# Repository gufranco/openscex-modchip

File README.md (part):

<div align="center">

<h1>openscex-modchip</h1>

<strong>Stealth SCEx region unlock for the PlayStation and PSone, on an ATtiny85 that <a href="src/trim.c">trims its own clock</a> against the console.</strong>

English | [日本語](README.ja.md) | [中文](README.zh.md)

<br>

<p>
  <a href="#quick-start">Quick start</a> |
  <a href="#console-tap-points">Wiring</a> |
  <a href="#status-indicator">Status indicator</a> |
  <a href="#against-other-chips">Comparison</a> |
  <a href="../../issues/new?template=compatibility.yml">Report your console</a>
</p>

</div>

[**6084**](Makefile) bytes of flash · [**8**](assets/psnee) board families, PU-7 to PM-41(2) · [**3**](src/region.c) regions · [**0**](AGENTS.md) MISRA deviations · [**100%**](tests/host) host line and branch coverage · [**669/669**](tools/mutate.py) mutants killed

```bash
gh release download --repo gufranco/openscex-modchip --pattern 'openscex-modchip-attiny85.hex' --pattern SHA256SUMS
sha256sum -c SHA256SUMS --ignore-missing
avrdude -c <programmer> -p attiny85 -U flash:w:openscex-modchip-attiny85.hex:i
```

> [!IMPORTANT]
> The current firmware passes the full simulation gate and has not yet run on a console. Measure the tap voltages before wiring. Source: [compatibility reports](https://github.com/gufranco/openscex-modchip/issues?q=label%3Acompatibility), [tests/sim](tests/sim).

Region-unlock firmware for the original PlayStation and the PSone, on an ATtiny85. It sends the configured region string only inside the SUBQ region-check window and keeps DATA high-impedance the rest of the time. It does not patch the boot ROM, so Japanese fat consoles and the PAL PSone also need a patched BIOS. It is not an optical-drive emulator, does not support PS2 or Saturn, and does not defeat LibCrypt. Source: [src/run.c](src/run.c), [src/inject.c](src/inject.c), [AGENTS.md](AGENTS.md).

| | | Source |
|:--|:--|:--|
| **Silent after acceptance**<br>No string starts after the first program-area frame; one already under way finishes, within 181 ms. Only a new lead-in read, such as an anti-mod TOC re-read, is served again. | **Disc swaps without a lid wire**<br>1.5 s without SUBQ frames counts as a swap and re-arms the chip for the next disc. | [src/inject.c](src/inject.c), [src/loop.c](src/loop.c), [src/run.c](src/run.c) |
| **Self-trimmed timing**<br>The chip times the console's 75 Hz SUBQ frames and trims its internal oscillator to within 1%. No clock wire. | **One region, one window**<br>Only the configured region string, only inside the SUBQ region-check window, at most 16 strings per arming. | [src/trim.c](src/trim.c), [src/region.c](src/region.c), [include/pscu/config.h](include/pscu/config.h) |
| **Status LED**<br>One pin reports boot stages, each disc's result and wiring faults. A final build only blinks briefly and reports each fault once. | **Proven in code**<br>MISRA C:2012 clean, 100% host coverage, a simavr console model, mutation testing, byte-identical rebuilds. | [src/indicator.c](src/indicator.c), [tests/host](tests/host), [tools/mutate.py](tools/mutate.py) |

## Overview

| Property | Value | Source |
|:---------|:------|:--|
| Console targets | PlayStation fat PU-7 through PU-23, PSone PM-41 and PM-41(2) | [assets/psnee](assets/psnee), [PsNee PSNee.ino L372-L406](https://github.com/kalymos/PsNee/blob/df52aec97d4e1677e3ed3ead1fba0bf102b1cfd7/PSNee/PSNee.ino#L372-L406) |
| MCU | ATtiny85 (8-pin DIP) | [include/port/registers.h](include/port/registers.h), [ATtiny25/45/85 datasheet 2586Q](https://ww1.microchip.com/downloads/en/DeviceDoc/Atmel-2586-AVR-8-bit-Microcontroller-ATtiny25-ATtiny45-ATtiny85_Datasheet.pdf) |
| Method | SCEx injection | [src/inject.c](src/inject.c), [psx-spx cdromdrive.md, SCEx](https://github.com/psx-spx/psx-spx.github.io/blob/6d7d1bc106a7e0b616b0330fe58401ab1ba57f0f/docs/cdromdrive.md#L1211-L1230) |
| Region | one per build, `REGION=jp\|us\|eu` (default us) | [Makefile](Makefile), [src/region.c](src/region.c) |
| Clock | the internal 8 MHz RC oscillator, trimmed against the console's SUBQ frame rate | [src/trim.c](src/trim.c), [ATtiny25/45/85 datasheet 2586Q](https://ww1.microchip.com/downloads/en/DeviceDoc/Atmel-2586-AVR-8-bit-Microcontroller-ATtiny25-ATtiny45-ATtiny85_Datasheet.pdf) |
| Wires | 4 signals (SQCK, SUBQ, DATA, WFCK) plus power; optional LED | [include/port/registers.h](include/port/registers.h), [PsNee MCU.h L453-L530](https://github.com/kalymos/PsNee/blob/df52aec97d4e1677e3ed3ead1fba0bf102b1cfd7/PSNee/MCU.h#L453-L530) |
| Toolchain | C17, MISRA C:2012 zero deviations, pinned Docker image | [Dockerfile](Dockerfile), [AGENTS.md](AGENTS.md) |

## Supported build per console

| Console | Board | `REGION` | Second region check | Source |
|:--------|:------|:---------|:--------------------|:--|
| Fat US/Canada, SCPH-1001 | PU-8 | `us` | none | [consolemods PS1 region information](https://consolemods.org/wiki/PS1:Region_Information), [PsNee PSNee.ino L10-L17](https://github.com/kalymos/PsNee/blob/df52aec97d4e1677e3ed3ead1fba0bf102b1cfd7/PSNee/PSNee.ino#L10-L17) |
| Fat US/Canada, SCPH-550x1/700x1/900x1 | PU-18 to PU-23 | `us` | none | [consolemods PS1 region information](https://consolemods.org/wiki/PS1:Region_Information), [PsNee PSNee.ino L10-L17](https://github.com/kalymos/PsNee/blob/df52aec97d4e1677e3ed3ead1fba0bf102b1cfd7/PSNee/PSNee.ino#L10-L17) |
| Fat PAL, SCPH-1002 | PU-8 | `eu` | none | [consolemods PS1 region information](https://consolemods.org/wiki/PS1:Region_Information), [PsNee PSNee.ino L10-L17](https://github.com/kalymos/PsNee/blob/df52aec97d4e1677e3ed3ead1fba0bf102b1cfd7/PSNee/PSNee.ino#L10-L17) |
| Fat PAL, SCPH-550x2/900x2 | PU-18 to PU-22 | `eu` | none | [consolemods PS1 region information](https://consolemods.org/wiki/PS1:Region_Information), [PsNee PSNee.ino L10-L17](https://github.com/kalymos/PsNee/blob/df52aec97d4e1677e3ed3ead1fba0bf102b1cfd7/PSNee/PSNee.ino#L10-L17) |
| PSone US/Canada, SCPH-101 | PM-41 / PM-41(2) | `us` | none | [consolemods PS1 region information](https://consolemods.org/wiki/PS1:Region_Information), [PsNee PSNee.ino L10-L17](https://github.com/kalymos/PsNee/blob/df52aec97d4e1677e3ed3ead1fba0bf102b1cfd7/PSNee/PSNee.ino#L10-L17) |
| PSone PAL, SCPH-102 | PM-41 / PM-41(2) | `eu` | in the boot ROM; needs a patched BIOS | [consolemods PS1 region information](https://consolemods.org/wiki/PS1:Region_Information), [PsNee PSNee.ino L33-L38](https://github.com/kalymos/PsNee/blob/df52aec97d4e1677e3ed3ead1fba0bf102b1cfd7/PSNee/PSNee.ino#L33-L38) |
| PSone Japan, SCPH-100 | PM-41 | `jp` | in the boot ROM; needs a patched BIOS | [consolemods PS1 region information](https://consolemods.org/wiki/PS1:Region_Information), [PsNee PSNee.ino L33-L38](https://github.com/kalymos/PsNee/blob/df52aec97d4e1677e3ed3ead1fba0bf102b1cfd7/PSNee/PSNee.ino#L33-L38) |
| Fat Japan, SCPH-1000/3000/3500/5000/5500/7000/7500/9000 | PU-7 to PU-23 | `jp` | in the boot ROM; needs a patched BIOS, though early SCPH-1000 units boot the disc anyway | [consolemods PS1 region information](https://consolemods.org/wiki/PS1:Region_Information), [PsNee PSNee.ino L33-L38](https://github.com/kalymos/PsNee/blob/df52aec97d4e1677e3ed3ead1fba0bf102b1cfd7/PSNee/PSNee.ino#L33-L38) |
| Asia, SCPH-xxx3 | unknown | `jp` | none | [consolemods PS1 region information](https://consolemods.org/wiki/PS1:Region_Information), [PsNee PSNee.ino L10-L17](https://github.com/kalymos/PsNee/blob/df52aec97d4e1677e3ed3ead1fba0bf102b1cfd7/PSNee/PSNee.ino#L10-L17) |
| Asia Video CD, SCPH-5903 | unknown | `jp` + `VCD_FILTER=on` | none | [consolemods PS1 region information](https://consolemods.org/wiki/PS1:Region_Information), [PsNee PSNee.ino L456-L490](https://github.com/kalymos/PsNee/blob/df52aec97d4e1677e3ed3ead1fba0bf102b1cfd7/PSNee/PSNee.ino#L456-L490) |

The PU-7 and PU-8 use the static-gate method, as in PsNee V9.0. Dev boards (DTL-H120x, PU-9) read burned discs natively and need no chip. Source: [PsNee PSNee.ino L33-L38](https://github.com/kalymos/PsNee/blob/df52aec97d4e1677e3ed3ead1fba0bf102b1cfd7/PSNee/PSNee.ino#L33-L38), [PsNee PSNee.ino L10-L17](https://github.com/kalymos/PsNee/blob/df52aec97d4e1677e3ed3ead1fba0bf102b1cfd7/PSNee/PSNee.ino#L10-L17), [PsNee PSNee.ino L456-L490](https://github.com/kalymos/PsNee/blob/df52aec97d4e1677e3ed3ead1fba0bf102b1cfd7/PSNee/PSNee.ino#L456-L490), [src/subq.c](src/subq.c).

## Quick start

Each [release](../../releases) carries prebuilt images: `us`, `eu`, `jp`, `jp-vcd` for the SCPH-5903, a quiet `-final` variant of each (see [Status indicator](#status-indicator)), a `SHA256SUMS` file, the license, `toolchain.spdx.json`, an SPDX bill of materials of the toolchain that built them, and a build-provenance attestation for every one of those files, the bill of materials included. Check a download before flashing it:

```bash
sha256sum -c SHA256SUMS --ignore-missing
gh attestation verify openscex-modchip-attiny85.hex --repo gufranco/openscex-modchip
```

Releases are versioned automatically from the commit history. To build from source, run every build, check and test through `make` in the pinned Docker toolchain; only `avrdude` runs on the host. Source: [.releaserc.json](.releaserc.json), [.github/workflows/release.yml](.github/workflows/release.yml).

| Tool | Purpose | Source |
|:-----|:--------|:--|
| Docker | runs the pinned toolchain | [Docker](https://docs.docker.com/get-docker/), [Dockerfile](Dockerfile) |
| Git | clones the repository | [Git](https://git-scm.com/downloads) |
| avrdude | flashes the image to the chip | [avrdude](https://github.com/avrdudes/avrdude) |
| Python 3.13 or later | runs make's Docker wrapper on the host | [Python](https://www.python.org/downloads/), [tools/docker_make.py](tools/docker_make.py), [pyproject.toml](pyproject.toml) |

```bash
git clone https://github.com/gufranco/openscex-modchip.git
cd openscex-modchip
make REGION=us                                        # America
make REGION=jp VCD_FILTER=on                          # SCPH-5903
make REGION=us PROFILE=final                          # America, quiet indicator
make REGION=us PROFILE=trace                          # America, debug trace on pin 2
avrdude -c <programmer> -p attiny85 -U flash:w:build/attiny85/release/openscex-modchip-attiny85.hex:i
avrdude -c <programmer> -p attiny85 -U lfuse:w:0xE2:m -U hfuse:w:0xDD:m -U efuse:w:0xFF:m
```

Any ISP works, including an Arduino as ISP. Write the flash first and the fuses last. The low fuse `0xE2` selects the internal 8 MHz oscillator, the slow-rising-power start-up delay and no clock divider (CKSEL 0010, SUT 10; datasheet Tables 6-6 and 6-7). The firmware also clears the clock prescaler at boot, so CKDIV8 cannot slow it. Reflashing erases the calibration record and oscillator trim; the chip learns them again. Source: [Arduino as ISP](https://docs.arduino.cc/built-in-examples/arduino-isp/ArduinoISP/), [ATtiny25/45/85 datasheet 2586Q](https://ww1.microchip.com/downloads/en/DeviceDoc/Atmel-2586-AVR-8-bit-Microcontroller-ATtiny25-ATtiny45-ATtiny85_Datasheet.pdf), [src/run.c](src/run.c).

A new ATtiny85 ships with CKDIV8 programmed and runs at 1 MHz, so the ISP clock must stay below 250 kHz until the fuses are written; the datasheet requires each half of the ISP clock to last more than two CPU cycles. An Arduino as ISP already does. With another programmer, add avrdude's `-B`, for example `-B 8`, for the first write. Source: [ATtiny25/45/85 datasheet 2586Q](https://ww1.microchip.com/downloads/en/DeviceDoc/Atmel-2586-AVR-8-bit-Microcontroller-ATtiny25-ATtiny45-ATtiny85_Datasheet.pdf), [avrdude manual, -B](https://avrdudes.github.io/avrdude/8.0/avrdude_3.html).

| Build | Fuses (low / high / extended) | Source |
|:------|:------------------------------|:--|
| Internal 8 MHz with brown-out detection at 2.7 V, recommended | `0xE2` / `0xDD` / `0xFF` | [ATtiny25/45/85 datasheet 2586Q](https://ww1.microchip.com/downloads/en/DeviceDoc/Atmel-2586-AVR-8-bit-Microcontroller-ATtiny25-ATtiny45-ATtiny85_Datasheet.pdf) |
| Internal 8 MHz without brown-out detection | `0xE2` / `0xDF` / `0xFF` | [ATtiny25/45/85 datasheet 2586Q](https://ww1.microchip.com/downloads/en/DeviceDoc/Atmel-2586-AVR-8-bit-Microcontroller-ATtiny25-ATtiny45-ATtiny85_Datasheet.pdf) |

Brown-out detection holds the chip in reset below 2.7 V, the ATtiny85's minimum supply for its speed grade; keep it on. The firmware also measures its supply before every string and holds back below about 2.75 V, shown as code 7. That limit still passes a 3.3 V supply 5 percent low on a chip whose bandgap reads high. Source: [ATtiny25/45/85 datasheet 2586Q](https://ww1.microchip.com/downloads/en/DeviceDoc/Atmel-2586-AVR-8-bit-Microcontroller-ATtiny25-ATtiny45-ATtiny85_Datasheet.pdf), [src/supply.c](src/supply.c).

Verify with the [Makefile](Makefile) targets:

```bash
make size        # image size; fails when less than 256 bytes of flash stay free
make test        # host tests, simavr console model and its stack check
make analyse     # formatting, lint, types, licences, MISRA and the Python tests
make repro       # every release image, built twice from clean, byte-identical
make mutate      # mutation testing on the logic layer
make mutate_platform  # mutation of run.c and engine.c, killed by the simulator
make bench_ci    # console bench: this firmware against PsNee in the same simulated console
```

CI runs the same gates on every push to `main` and every pull request, as defined in [`.github/workflows/ci.yml`](.github/workflows/ci.yml). `make mutate_platform` runs in its own workflow, [`.github/workflows/mutation.yml`](.github/workflows/mutation.yml), whenever the firmware, the simulator suite, the mutation tool or the pinned toolchain changes. `make hooks` enables the commit-message and formatting checks locally.

## MCU pinout

The four SCEx signals and the indicator pin keep PsNee's ATtiny85 assignment from its `MCU.h`, so PsNee wiring guides match pin for pin. PB5 stays RESET, so the chip remains ISP-programmable. Pin numbers are for the 8-pin PDIP; check the datasheet for SOIC. Source: [PsNee MCU.h L453-L530](https://github.com/kalymos/PsNee/blob/df52aec97d4e1677e3ed3ead1fba0bf102b1cfd7/PSNee/MCU.h#L453-L530), [include/port/registers.h](include/port/registers.h), [ATtiny25/45/85 datasheet 2586Q](https://ww1.microchip.com/downloads/en/DeviceDoc/Atmel-2586-AVR-8-bit-Microcontroller-ATtiny25-ATtiny45-ATtiny85_Datasheet.pdf).

| DIP pin | Port | Signal | Direction | Connect to | Source |
|:-------:|:-----|:-------|:----------|:-----------|:--|
| 1 | PB5 | RESET | - | leave as reset | [include/port/registers.h](include/port/registers.h), [ATtiny25/45/85 datasheet 2586Q](https://ww1.microchip.com/downloads/en/DeviceDoc/Atmel-2586-AVR-8-bit-Microcontroller-ATtiny25-ATtiny45-ATtiny85_Datasheet.pdf) |
| 2 | PB3 | INDICATOR | out, optional | status LED through a 1 kΩ resistor, or leave off | [include/port/registers.h](include/port/registers.h), [PsNee PSNee.ino L64](https://github.com/kalymos/PsNee/blob/df52aec97d4e1677e3ed3ead1fba0bf102b1cfd7/PSNee/PSNee.ino#L64) |
| 3 | PB4 | WFCK | in and out | static gate, or PU-22+ live carrier | [include/port/registers.h](include/port/registers.h), [PsNee MCU.h L453-L530](https://github.com/kalymos/PsNee/blob/df52aec97d4e1677e3ed3ead1fba0bf102b1cfd7/PSNee/MCU.h#L453-L530) |
| 4 | GND | GND | - | console ground | [ATtiny25/45/85 datasheet 2586Q](https://ww1.microchip.com/downloads/en/DeviceDoc/Atmel-2586-AVR-8-bit-Microcontroller-ATtiny25-ATtiny45-ATtiny85_Datasheet.pdf) |
| 5 | PB0 | SQCK | in | SUBQ serial clock | [include/port/registers.h](include/port/registers.h), [PsNee MCU.h L453-L530](https://github.com/kalymos/PsNee/blob/df52aec97d4e1677e3ed3ead1fba0bf102b1cfd7/PSNee/MCU.h#L453-L530) |
| 6 | PB1 | SUBQ | in | SUBQ serial data | [include/port/registers.h](include/port/registers.h), [PsNee MCU.h L453-L530](https://github.com/kalymos/PsNee/blob/df52aec97d4e1677e3ed3ead1fba0bf102b1cfd7/PSNee/MCU.h#L453-L530) |
| 7 | PB2 | DATA | out, drive-low or high-Z | SCEx injection into the mechacon | [include/port/registers.h](include/port/registers.h), [src/port.S](src/port.S) |
| 8 | VCC | VCC | - | console supply, measure first | [ATtiny25/45/85 datasheet 2586Q](https://ww1.microchip.com/downloads/en/DeviceDoc/Atmel-2586-AVR-8-bit-Microcontroller-ATtiny25-ATtiny45-ATtiny85_Datasheet.pdf) |

## Console tap points

The photos below label SQCK, SUBQ, DATA, WFCK, VCC and GND on each board; solder each wire where they are marked. The PU-18 photo shows the underside. Leave AX, DX and RESET unconnected: they belong to PsNee's boot-ROM patch. Source: [assets/psnee](assets/psnee).

<table>
<tr><td align="center" width="33%"><br><sub><b>PU-7</b>. Photo from PsNee</sub></td><td align="center" width="33%"><br><sub><b>PU-8</b>, 1-658-467-22. Photo from PsNee</sub></td><td align="center" width="33%"><br><sub><b>PU-8</b>, 1-658-467-12. Photo from PsNee</sub></td></tr>
<tr><td align="center" width="33%"><br><sub><b>PU-18</b>. Photo from PsNee</sub></td><td align="center" width="33%"><br><sub><b>PU-20</b>. Photo from PsNee</sub></td><td align="center" width="33%"><br><sub><b>PU-22</b>. Photo from PsNee</sub></td></tr>
<tr><td align="center" width="33%"><br><sub><b>PU-23</b>. Photo from PsNee</sub></td><td align="center" width="33%"><br><sub><b>PM-41</b>. Photo from PsNee</sub></td><td align="center" width="33%"><br><sub><b>PM-41(2)</b>. Photo from PsNee</sub></td></tr>
</table>

These nine photos come from [PsNee](https://github.com/kalymos/PsNee) V9.0 by kalymos and its contributors, released into the public domain under the [Unlicense](LICENSES/Unlicense.txt), and are copied here resized.

| Board family | SCPH era | DATA injection point | WFCK role | Source |
|:-------------|:---------|:---------------------|:----------|:--|
| PU-7, PU-8, PU-18, PU-20 | 1000-750x | digital NRZ output of the wobble ASIC into the mechacon | static gate | [assets/psnee](assets/psnee), [PsNee PSNee.ino L372-L406](https://github.com/kalymos/PsNee/blob/df52aec97d4e1677e3ed3ead1fba0bf102b1cfd7/PSNee/PSNee.ino#L372-L406) |
| PU-22, PU-23 | 7500-900x | CD-processor tracking line, WFCK as a fake carrier, three-wire-plus-link | live clock, sync required | [assets/psnee](assets/psnee), [PsNee PSNee.ino L372-L406](https://github.com/kalymos/PsNee/blob/df52aec97d4e1677e3ed3ead1fba0bf102b1cfd7/PSNee/PSNee.ino#L372-L406) |
| PM-41, PM-41(2) | PSone 100-103 | same tracking-line carrier method; float the chip I/O when idle on PM-41(2) | live clock | [assets/psnee](assets/psnee), [quade.co PsNee guide](https://quade.co/ps1-modchip-guide/psnee/) |

With no clock or lid wire, the chip can sit anywhere the four signal wires reach. Keep those wires short: long wires pick up noise, a known cause of Mayumi V4 failures (quade.co). Remove the clock and lid wires of an install made for an earlier release before flashing this firmware, because pin 2 is now PB3, the indicator output, and would drive against a console clock left there. Source: [src/trim.c](src/trim.c), [src/loop.c](src/loop.c), [quade.co Mayumi V4 guide](https://quade.co/ps1-modchip-guide/mayumi-v4/), [include/port/registers.h](include/port/registers.h).

## Board

One optional board holds the chip in a DIP-8 socket, so it comes out for reflashing. The console wires land on six 4 by 4 mm top-side pads with no holes, 6 mm apart along the bottom edge: WFCK, SQCK, SUBQ, DATA, VCC and GND. Every part is through-hole. The socket, a 100 nF decoupling capacitor, a 220 µF bulk capacitor and a 10 kΩ RESET pull-up are always fitted, the pull-up because the chip's internal one is weak against console noise. Three headers are optional and marked "opt" on the board, so a build fits only what it uses. The board is a KiCad 10 project with its schematic, layout and design rules, 35.6 × 34.3 mm. Source: [hardware/openscex.kicad_sch](hardware/openscex.kicad_sch), [hardware/openscex.kicad_pcb](hardware/openscex.kicad_pcb).

| Part | Fit | Purpose | Source |
|:--|:--|:--|:--|
| U1, DIP-8 socket | always | holds the ATtiny85 | [hardware/openscex.kicad_sch](hardware/openscex.kicad_sch) |
| C1, 100 nF ceramic | always | answers the chip's fast current edges at its supply pins | [hardware/openscex.kicad_sch](hardware/openscex.kicad_sch) |
| C2, 220 µF electrolytic | always | holds the supply up through pulsed loads on J2, such as an active buzzer, whose pulses would otherwise dip it through the thin supply wire; 11.2 mm tall, it may be laid flat on its leads | [hardware/openscex.kicad_sch](hardware/openscex.kicad_sch), [Panasonic FC series](https://industrial.panasonic.com/cdbs/www-data/pdf/RDF0000/ABA0000C1209.pdf) |
| R1, 10 kΩ | always | holds RESET high | [hardware/openscex.kicad_sch](hardware/openscex.kicad_sch) |
| J1, keyed 2×3 ISP header | optional | reflashing the chip | [hardware/openscex.kicad_sch](hardware/openscex.kicad_sch) |
| J2, keyed JST XH 3-pin header | optional | pin 1 GND, pin 2 VCC, pin 3 PB3 (SIG on the board), for a cable to the indicator of your choice: an LED with its resistor, an active buzzer, or a board of your own | [hardware/openscex.kicad_sch](hardware/openscex.kicad_sch), [JST XH datasheet](https://www.jst-mfg.com/product/pdf/eng/eXH.pdf) |
| J3, 6-pin header | optional | the trace image's serial line, for an FTDI TTL-232R cable | [hardware/openscex.kicad_sch](hardware/openscex.kicad_sch) |

<table>
<tr><td align="center" width="33%"><br><sub><b>The board</b>, 3D view</sub></td><td align="center" width="33%"><br><sub><b>The board</b>, top</sub></td><td align="center" width="33%"><br><sub><b>The board</b>, bottom, the ground plane</sub></td></tr>
</table>

The board is symmetric about its vertical centre line: the chip, the serial header and the row of wire pads sit on it, and the ISP header on the left is balanced by the indicator header, R1 and C1 on the right. It has two layers laid out against noise. Every track is as wide as its route allows, 1.0 mm on this board; tracks run on top where they can, so the bottom stays a ground plane under the console lines; both layers are ground-poured and stitched with 0.6 mm vias; every bend is a tangent arc of at most 45 degrees; different nets keep 1 mm apart and 0.8 mm from pads. Source: [hardware/openscex.kicad_pcb](hardware/openscex.kicad_pcb), [hardware/openscex.kicad_dru](hardware/openscex.kicad_dru).

The ISP header follows the AVR 6-pin layout: 1 MISO on SUBQ, 2 VCC, 3 SCK on DATA, 4 MOSI on SQCK, 5 RESET, 6 GND. Its keyed shroud keeps 1.5 mm clear of every other part. Reflash with the board out of the console or its wires unsoldered; in place, the programmer would feed the console's supply and fight the console's drivers on SQCK and SUBQ. Source: [hardware/openscex.kicad_sch](hardware/openscex.kicad_sch), [ATtiny25/45/85 datasheet 2586Q](https://ww1.microchip.com/downloads/en/DeviceDoc/Atmel-2586-AVR-8-bit-Microcontroller-ATtiny25-ATtiny45-ATtiny85_Datasheet.pdf).

J2 is a keyed JST XH header, so its plug goes in one way only. Its pins follow the RC servo order, GND, VCC, signal: VCC in the middle never meets a ground wire, so even a plug forced in reversed powers nothing backwards. VCC powers whatever the cable leads to, such as a buzzer module or a board of your own; a plain LED needs only GND and SIG. VCC is the console's 3.5 V rail, so a cable must never join it to GND. Source: [hardware/openscex.kicad_sch](hardware/openscex.kicad_sch), [JST XH datasheet](https://www.jst-mfg.com/product/pdf/eng/eXH.pdf).

The serial header J3 takes the 6-way socket of an FTDI TTL-232R cable: pin 1 is GND, pin 5 the cable's RXD input, and pins 2, 3, 4 and 6 stay open, so the cable's 5 V output never reaches the console. It stands at the top edge with 2 mm clear around it, so the socket meets no other part. J2 and J3 both carry PB3, and the image flashed decides what PB3 is, so plug only the cable that matches it: the indicator cable for `debug` or `final`, the serial cable for `trace`. Source: [hardware/openscex.kicad_sch](hardware/openscex.kicad_sch), [hardware/openscex.kicad_pcb](hardware/openscex.kicad_pcb), [TTL-232R datasheet](https://www.farnell.com/datasheets/81225.pdf).

The board has a bill of materials, whose Fit column names the optional parts, and a Gerber and drill archive ready for a board house, both exported with KiCad 10.0.6. Teardrops are drawn into the board, so the archive needs no refill in KiCad. Source: [hardware/openscex-bom.csv](hardware/openscex-bom.csv), [hardware/fab/openscex-gerbers.zip](hardware/fab/openscex-gerbers.zip).

## Safety

- Measure the voltage at every tap point before wiring. Every board, PU-7 to PM-41(2), runs most of its chips from +3.5 V, and that is the chip's supply; the board's +5 V rail feeds a few parts such as the AV multi out, the audio amplifier and the regulator for the sound and CD supply, and PsNee warns against wiring the chip to it. Source: [psx-spx pinouts.md, voltage summary](https://github.com/psx-spx/psx-spx.github.io/blob/6d7d1bc106a7e0b616b0330fe58401ab1ba57f0f/docs/pinouts.md#L1777-L1795), [PsNee changelog](https://github.com/kalymos/PsNee/blob/df52aec97d4e1677e3ed3ead1fba0bf102b1cfd7/changelog#L38).
- Opening a console and soldering to the CD subsystem can destroy it. Build at your own risk. Source: [quade.co PS1 modchip guide](https://quade.co/ps1-modchip-guide/).

## Status indicator

PB3 drives an optional indicator, usually an LED, the chip's only diagnostic channel. It shows the current stage, whether each disc passed its region check, and which wire to check when something fails. It never delays or gates a feature and keeps no history, so every code except the two boot codes describes the present. Source: [src/indicator.c](src/indicator.c).

| Part | Choice | Source |
|:-----|:-------|:--|
| LED | a 3 mm or 5 mm red, orange, yellow or green LED, forward voltage about 2 V; not blue or white, whose 3 V forward voltage leaves almost nothing across the resistor on the console's 3.5 V supply | [Kingbright WP7113ID datasheet](https://www.kingbrightusa.com/images/catalog/SPEC/WP7113ID.pdf), [ATtiny25/45/85 datasheet 2586Q](https://ww1.microchip.com/downloads/en/DeviceDoc/Atmel-2586-AVR-8-bit-Microcontroller-ATtiny25-ATtiny45-ATtiny85_Datasheet.pdf) |
| Resistor | 1 kΩ, any wattage: about 1.5 mA at the console's 3.5 V, well under the pin's 40 mA absolute maximum | [ATtiny25/45/85 datasheet 2586Q](https://ww1.microchip.com/downloads/en/DeviceDoc/Atmel-2586-AVR-8-bit-Microcontroller-ATtiny25-ATtiny45-ATtiny85_Datasheet.pdf) |
| LED wiring | pin 2 (PB3), or pin 3 of the board's header J2, to the resistor, the resistor to the LED anode (long leg), the cathode (flat side) to ground, or pin 1 of J2; on the board the LED and its resistor ride on the cable, so the LED can sit anywhere in the case | [include/port/registers.h](include/port/registers.h), [hardware/openscex.kicad_sch](hardware/openscex.kicad_sch) |

Two builds drive the pin. `debug`, the default, shows everything below; `final`, built with `make PROFILE=final` and released as the `-final` images, stays quiet. Flash `debug` to install and troubleshoot, then `final` to play. Only the pin differs: the simulator checks edge by edge that both send the same strings at the same times. Source: [include/pscu/indicator.h](include/pscu/indicator.h), [tests/sim/sim_profile.c](tests/sim/sim_profile.c).

| Stage | debug | final | Source |
|:------|:------|:------|:--|
| Board detection | lit for about 0.4 s after power-on | dark | [src/engine.c](src/engine.c) |
| Board found | one 300 ms blink for a static-gate board (PU-18, PU-20), two for a WFCK-carrier board (PU-22 and later) | one 60 ms blink for a static-gate board, two for a WFCK-carrier board | [src/indicator.c](src/indicator.c) |
| Waiting for a disc | a 40 ms blip every 2 s | dark | [src/indicator.c](src/indicator.c) |
| Injecting | a 90 to 181 ms flash per region string | dark | [src/engine.c](src/engine.c) |
| Result | a code shown three times, then dark | an accepted disc gives one 60 ms blink, a refused one code 2 twice; then dark | [src/indicator.c](src/indicator.c) |
| Play | dark, with a 40 ms tick each time OSCCAL moves or the calibration is written | dark | [src/indicator.c](src/indicator.c), [src/run.c](src/run.c) |

Codes are long 700 ms flashes, 300 ms apart, with a 2 s pause before the code repeats. In `final`, codes 3 and 4 play once per disc, and code 7 repeats every 30 s while it holds. Source: [src/indicator.c](src/indicator.c).

| Code | Meaning | Check | Source |
|:----:|:--------|:------|:--|
| 1 | the console accepted the region string | nothing, the disc plays | [src/indicator.c](src/indicator.c), [src/loop.c](src/loop.c) |
| 2 | strings were sent and the console never reached the program area | DATA and WFCK wiring, and that the build's region matches the disc | [src/indicator.c](src/indicator.c), [src/loop.c](src/loop.c) |
| 3 | no SUBQ frame for 5 s after power-on; shown for 15 s, then the heartbeat | SQCK, SUBQ, power and ground; also shown with no disc in | [src/indicator.c](src/indicator.c), [src/loop.c](src/loop.c) |
| 4 | frames arrive but no region check for 20 s; repeats while it holds | SUBQ; also normal with an audio CD | [src/indicator.c](src/indicator.c), [src/loop.c](src/loop.c) |
| 5 | the watchdog reset the chip, shown once at the next boot | the supply and ground: a dip or noise stopped the main loop | [src/indicator.c](src/indicator.c), [src/port_chip.S](src/port_chip.S) |
| 6 | the board differs from the one the calibration stored, shown once at boot; code 5 takes priority | the WFCK wire, which is intermittent, unless the chip moved to another console | [src/indicator.c](src/indicator.c), [src/calib.c](src/calib.c) |
| 7 | the supply measured under about 2.75 V, or the reading failed; no string is sent while it holds, and it outranks codes 3 and 4 | VCC and ground at the tap points, which must measure 3.3 V or more | [src/indicator.c](src/indicator.c), [src/supply.c](src/supply.c) |

### Serial trace

`make PROFILE=trace` builds an image that turns pin 2 (PB3) into a serial line instead of the indicator, at 115200 baud, 8N1. It carries everything needed to find a fault without an oscilloscope: a boot report, every SUBQ frame the chip captured, and a line for every decision it took, each with its time since power-on. The lines go out in the gap after each frame, at most one decision per gap, so DATA sends the same strings with the same bit timing as the other two images, each string starting at most one frame later, which the simulator checks edge by edge. Source: [src/trace.c](src/trace.c), [src/run.c](src/run.c), [tests/sim/sim_trace.c](tests/sim/sim_trace.c), [tests/sim/sim_profile.c](tests/sim/sim_profile.c).

To connect it on the board, plug a TTL-232R cable onto the serial header J3, black wire on GND, with no indicator cable on J2. On a bare chip, wire pin 2 to the RX input of a USB serial adapter and its ground to the console's ground. The line swings between 0 and the console's 3.5 V logic supply, which a 3.3 V adapter such as the TTL-232R-3V3 reads. Start the capture before powering the console, so the boot report is in it. Source: [hardware/openscex.kicad_sch](hardware/openscex.kicad_sch), [TTL-232R datasheet](https://www.farnell.com/datasheets/81225.pdf), [psx-spx pinouts.md, voltage summary](https://github.com/psx-spx/psx-spx.github.io/blob/6d7d1bc106a7e0b616b0330fe58401ab1ba57f0f/docs/pinouts.md#L1777-L1795).

```sh
# Linux; on macOS the port is /dev/cu.usbserial-*, and stty takes -f
stty -F /dev/ttyUSB0 115200 raw && cat /dev/ttyUSB0 | tee capture.txt
python3 tools/serial_trace.py capture.txt
```

Each frame line is the 12 SUBQ bytes in hex; a failed capture reads as all `F`. Every other line starts with `@` and the time, such as `@1.460 OPEN 0A 0A`, in seconds and milliseconds since power-on. Source: [src/trace.c](src/trace.c).

| Line | Meaning | Source |
|:--|:--|:--|
| `BOOT US 1A2B` | the region built in and the first four hex digits of the commit; a trailing `V` means the Video CD filter | [src/trace.c](src/trace.c), [Makefile](Makefile) |
| `RST PWR`, `RST WDT` | started from power-on, or restarted by the watchdog after the main loop stalled | [src/trace.c](src/trace.c), [src/port_chip.S](src/port_chip.S) |
| `BRD W D` | the board: `W` WFCK carrier or `G` static gate; then `D` detected, `K` kept from the record after a watchdog reset, or `C` detected and not the board recorded | [src/trace.c](src/trace.c), [src/calib.c](src/calib.c) |
| `OSC 50>4E` | OSCCAL from its factory value to the value applied, and later each trim step against the 75 Hz frame rate | [src/trace.c](src/trace.c), [src/trim.c](src/trim.c) |
| `REC W 0C P -2` | the calibration record: board, start in hex, `F` frozen or `P` still probing, and the trim; at boot as read from EEPROM, later each time it is learned | [src/trace.c](src/trace.c), [src/calib.c](src/calib.c) |
| `SUP OK 3303mV`, `SUP LOW 2601mV` | the supply at boot and each time it crosses the 2.75 V guard; below it no string is sent and no record written | [src/trace.c](src/trace.c), [src/supply.c](src/supply.c) |
| `DISC`, `GONE` | valid SUBQ frames again, or none for 1.5 s | [src/trace.c](src/trace.c), [src/inject.c](src/inject.c) |
| `OPEN 0A 0A` | the window opened: the SUBQ counter and the start it reached, in hex | [src/trace.c](src/trace.c), [src/loop.c](src/loop.c) |
| `HOLD 03 0A 3303mV` | the window held without sending: under the supply guard, or just below the start after it opened | [src/trace.c](src/trace.c), [src/loop.c](src/loop.c) |
| `SHUT P 00` | the window shut: `P` a program-area frame, `G` the disc left, `D` the counter fell back | [src/trace.c](src/trace.c), [src/loop.c](src/loop.c) |
| `SCEX 3 W` | string 3 of at most 16 in this opening, and the board mode it was sent in | [src/trace.c](src/trace.c), [src/engine.c](src/engine.c) |
| `PASS`, `FAIL` | the console went on to the program area after the strings, or did not in time | [src/trace.c](src/trace.c), [src/loop.c](src/loop.c) |
| `MISS 0B 0C` | the lead-in ended before the window opened: how far the counter got and the start it needed; the start moves earlier for the next disc | [src/trace.c](src/trace.c), [src/calib.c](src/calib.c) |
| `SAVE OK`, `SAVE NO 2601mV` | the record written to EEPROM, or refused for a low supply and kept to try again | [src/trace.c](src/trace.c), [src/engine.c](src/engine.c) |
| `LOST 2` | events dropped because more came in a row than the four-event queue holds | [src/trace.c](src/trace.c), [include/pscu/trace.h](include/pscu/trace.h) |

`tools/serial_trace.py` reads a saved capture, or the terminal piped into it, and prints the timeline in words, with each frame's place on the disc and its CRC checked and runs of the same frame folded into one line. It ends with a diagnosis that names the likely fault and what to check: no frame or every capture failed points to the SQCK and SUBQ wires, many bad CRCs to noise on them, watchdog restarts to a supply dip or noise that stopped the main loop, repeated power-on starts or a low supply to the power tap, a lead-in that never opens the window to the learned start, strings without `PASS` to the DATA and WFCK wires or a region mismatch, and `PASS` with a game that still stops to an anti-mod check or a boot-ROM region check. `--summary` prints the diagnosis alone. Source: [tools/serial_trace.py](tools/serial_trace.py), [tests/serial_trace/test_serial_trace.py](tests/serial_trace/test_serial_trace.py).

## How it works

```mermaid
graph LR
    subgraph Console
        CD[CD subsystem]
        WF[WFCK]
        MECH[Mechacon]
    end
    subgraph ATtiny85
        CAP[SUBQ capture]
        DET[Region-check detector]
        ST[Stealth state machine]
        INJ[SCEx injector]
        IND[Status indicator]
        CAL[Per-console calibration]
    end
    CD -->|SQCK, SUBQ| CAP
    CAP --> DET --> ST --> INJ
    ST --> IND
    ST <-->|start| CAL
    WF -->|gate or carrier| INJ
    INJ -->|DATA| MECH
```

## What's included

| Feature | Detail | Source |
|:--------|:-------|:--|
| SCEx injection | 44-bit LSB-first region string; the static-gate method on PU-7 to PU-20, with WFCK held low for each string as in PsNee and Mayumi V4, and the WFCK-carrier method on PU-22 and later | [src/inject.c](src/inject.c), [src/port.S](src/port.S), [PsNee PSNee.ino L53](https://github.com/kalymos/PsNee/blob/df52aec97d4e1677e3ed3ead1fba0bf102b1cfd7/PSNee/PSNee.ino#L53) |
| Board auto-detect | WFCK at boot selects gate or carrier mode, so one build fits every family. A carrier needs 25 unbroken WFCK edges, each within 360 µs of the last, as MultiMode 3 and Mayumi V4 require. On a gate board WFCK is watched again for 13.1 ms before each string, so a late-starting carrier is never held low. After a watchdog reset the board recorded at boot is kept, so a stalled carrier is not driven as a gate | [src/board_mode.c](src/board_mode.c), [src/engine.c](src/engine.c), [src/calib.c](src/calib.c), [PsNee PSNee.ino L372-L406](https://github.com/kalymos/PsNee/blob/df52aec97d4e1677e3ed3ead1fba0bf102b1cfd7/PSNee/PSNee.ino#L372-L406) |
| Supply guard | before every string the chip measures its supply against its 1.1 V bandgap; below about 2.75 V, or on an impossible reading, it sends nothing and shows code 7. A brief dip pauses a burst without restarting its count, and a window kept shut teaches the calibration nothing | [src/supply.c](src/supply.c), [src/port_chip.S](src/port_chip.S), [ATtiny25/45/85 datasheet 2586Q](https://ww1.microchip.com/downloads/en/DeviceDoc/Atmel-2586-AVR-8-bit-Microcontroller-ATtiny25-ATtiny45-ATtiny85_Datasheet.pdf) |
| Oscillator trim | times the console's 75 Hz SUBQ frames in the lead-in and in play, and steps OSCCAL up to 4 notches per batch, one per write, until within 1%, never more than 16 notches from the factory value; the trim is stored in EEPROM and applied at boot | [src/trim.c](src/trim.c), [src/run.c](src/run.c), [ATtiny25/45/85 datasheet 2586Q](https://ww1.microchip.com/downloads/en/DeviceDoc/Atmel-2586-AVR-8-bit-Microcontroller-ATtiny25-ATtiny45-ATtiny85_Datasheet.pdf) |
| Disc swaps | no lid wire: 1.5 s without a valid SUBQ frame, which only a stopped drive gives, re-arms the chip; seeks and rereads keep producing frames. The SUBQ counter stops 8 frames past the start, so the window closes within about half a second after a lid opens, even on a refused disc. Every disc may get the full 16-string cap | [src/inject.c](src/inject.c), [src/loop.c](src/loop.c), [include/pscu/loop.h](include/pscu/loop.h) |
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
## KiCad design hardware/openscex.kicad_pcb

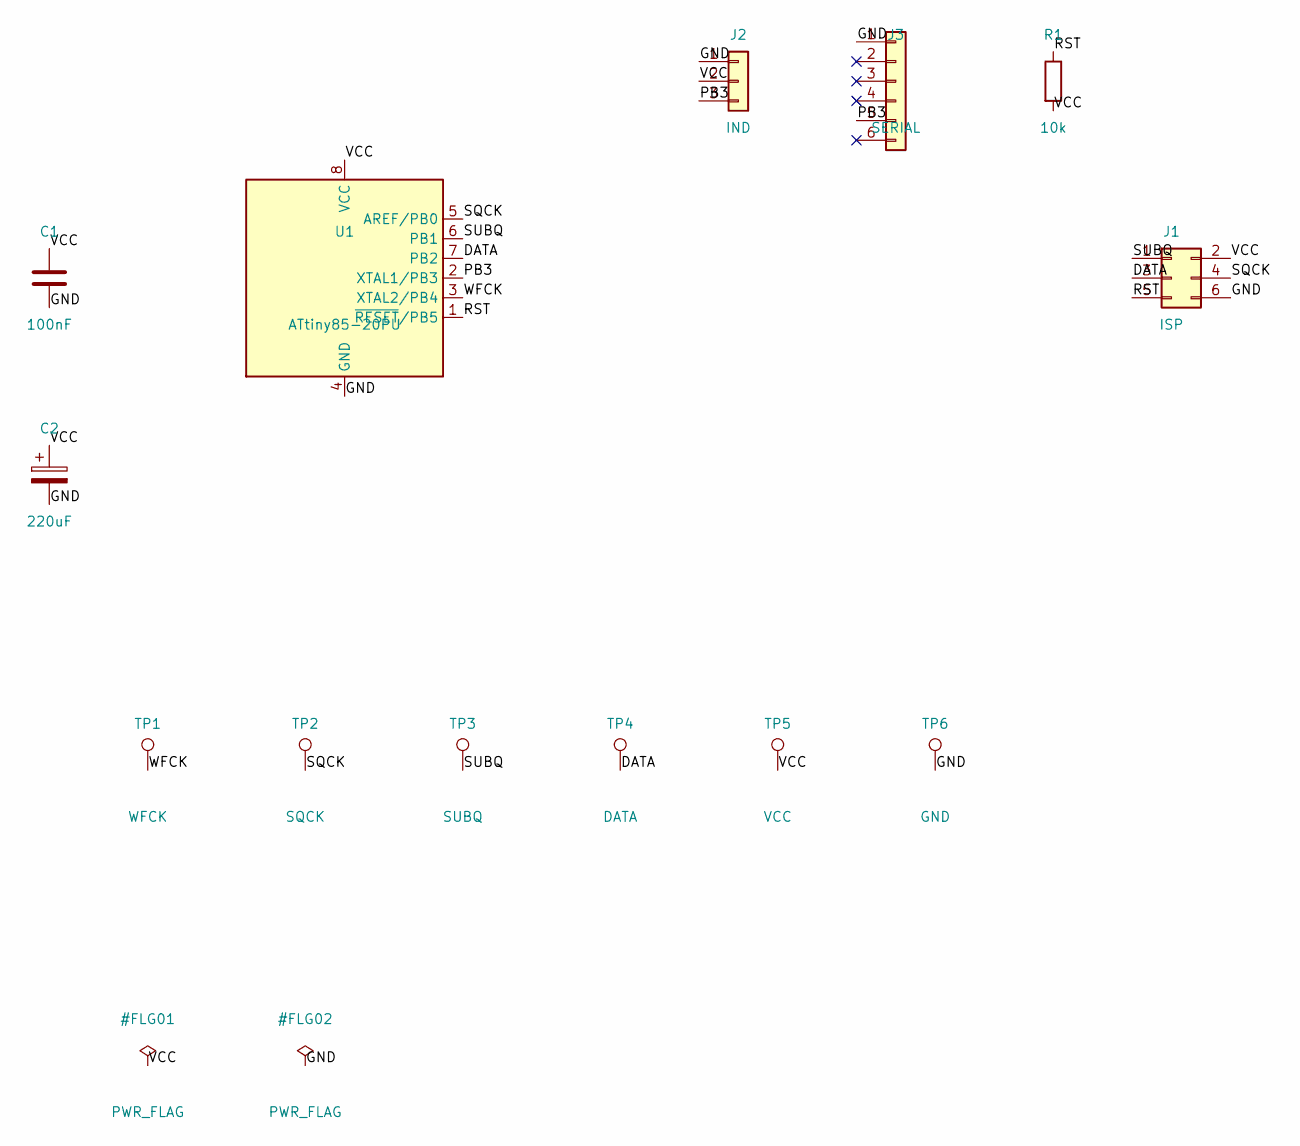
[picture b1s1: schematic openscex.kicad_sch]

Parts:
C1: 100nF; C_Rect_L4.0mm_W2.5mm_P2.50mm; Part KEMET C315C104K5R5TA, 100 nF 50 V X7R, 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
C2: 220uF; CP_Radial_D6.3mm_P2.50mm; Part Panasonic EEU-FC1A221S, 220 uF 10 V, 10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
J1: ISP; IDC-Header_2x03_P2.54mm_Vertical_Wurth_61200621621; Part Wurth 61200621621, 2x3 box header, 2.54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
J2: IND; JST_XH_B3B-XH-A_1x03_P2.50mm_Vertical; Part JST B3B-XH-A(LF)(SN), 3-pin XH header, 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
J3: SERIAL; PinHeader_1x06_P2.54mm_Vertical; Part Wurth 61300611121, 1x6 pin header, 2.54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
R1: 10k; R_Axial_DIN0204_L3.6mm_D1.6mm_P5.08mm_Horizontal; Part Vishay MBA02040C1002FC100, 10 kOhm 1 % 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
TP1: WFCK; TestPoint_Pad_4.0x4.0mm
TP2: SQCK; TestPoint_Pad_4.0x4.0mm
TP3: SUBQ; TestPoint_Pad_4.0x4.0mm
TP4: DATA; TestPoint_Pad_4.0x4.0mm
TP5: VCC; TestPoint_Pad_4.0x4.0mm
TP6: GND; TestPoint_Pad_4.0x4.0mm
U1: ATtiny85-20PU; DIP-8_W7.62mm_Socket; Part Microchip ATTINY85-20PU in a TE 1-21992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

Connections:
/DATA: J1.3, TP4.1, U1.7 (PB2)
/GND: C1.2, C2.2, J1.6, J2.1, J3.1, TP6.1, U1.4 (GND)
/PB3: J2.3, J3.5, U1.2 (XTAL1/PB3)
/RST: J1.5, R1.1, U1.1 (~RESET/PB5)
/SQCK: J1.4, TP2.1, U1.5 (AREF/PB0)
/SUBQ: J1.1, TP3.1, U1.6 (PB1)
/VCC: C1.1, C2.1, J1.2, J2.2, R1.2, TP5.1, U1.8 (VCC)
/WFCK: TP1.1, U1.3 (XTAL2/PB4)

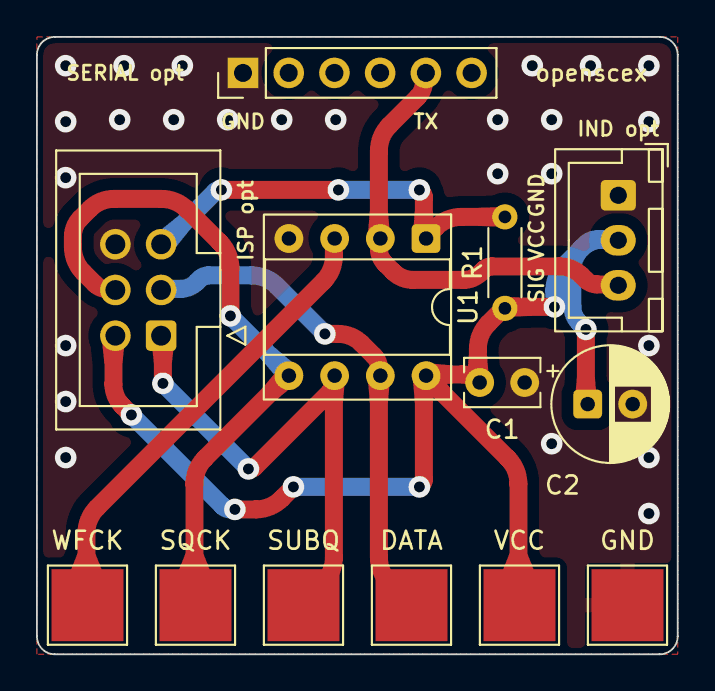
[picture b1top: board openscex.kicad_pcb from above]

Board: 2 copper layers, 35.6 x 34.3 mm, 13 parts (0 on the bottom side), 8 nets.

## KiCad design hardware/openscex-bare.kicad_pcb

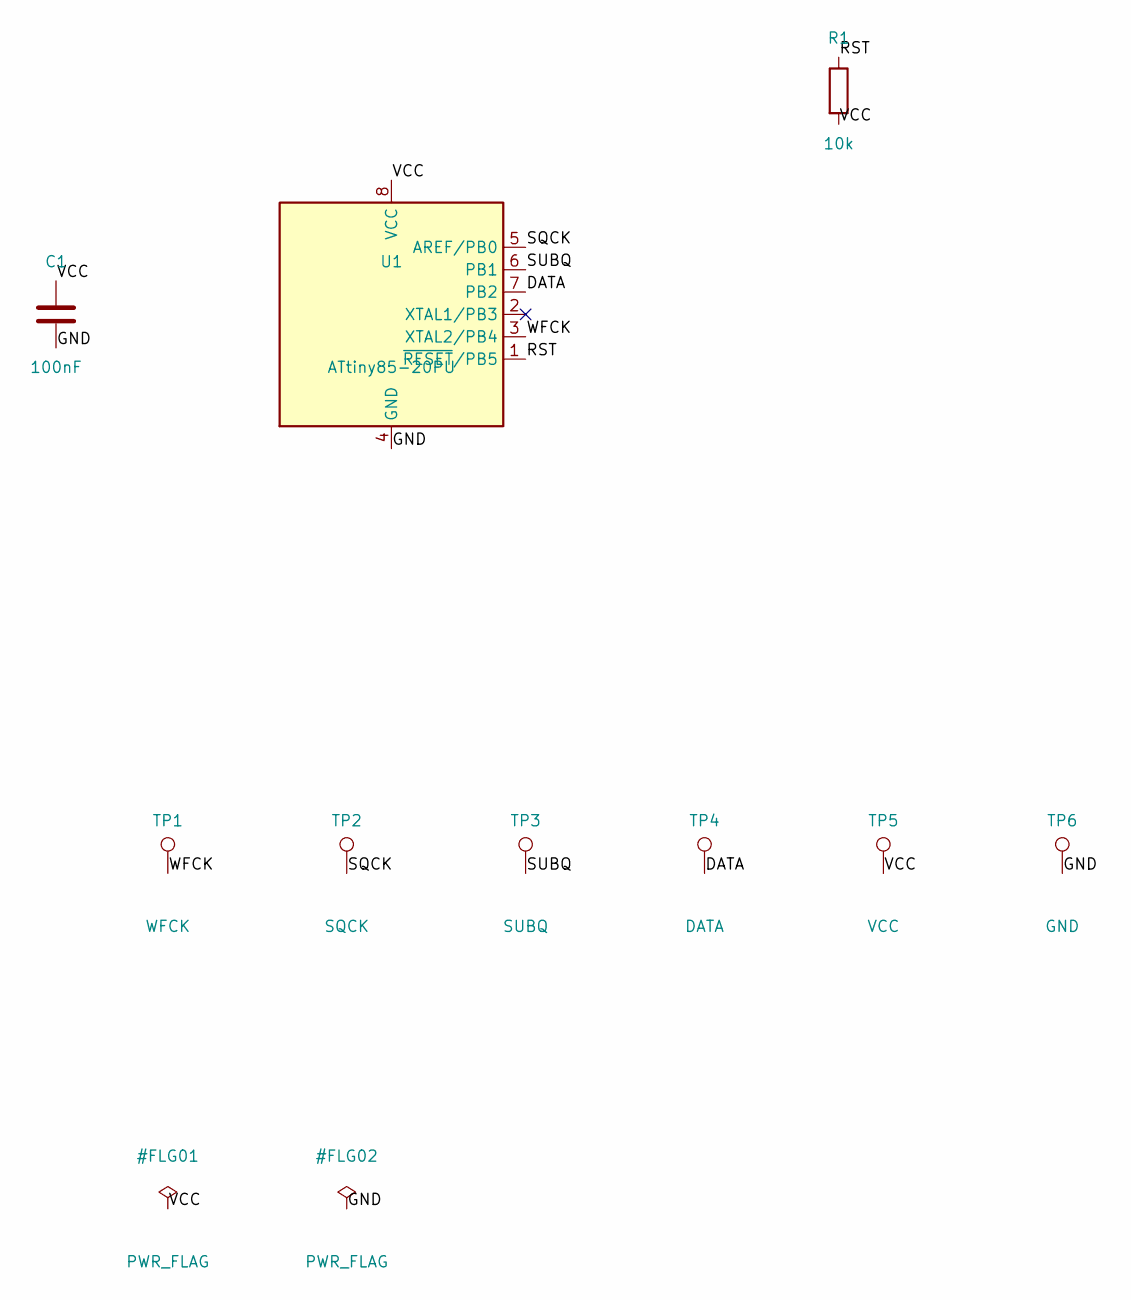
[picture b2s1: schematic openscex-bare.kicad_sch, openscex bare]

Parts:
C1: 100nF; C_Rect_L4.0mm_W2.5mm_P2.50mm; Part KEMET C315C104K5R5TA, 100 nF 50 V X7R, 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
R1: 10k; R_Axial_DIN0204_L3.6mm_D1.6mm_P5.08mm_Horizontal; Part Vishay MBA02040C1002FC100, 10 kOhm 1 % 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
TP1: WFCK; TestPoint_Pad_4.0x4.0mm
TP2: SQCK; TestPoint_Pad_4.0x4.0mm
TP3: SUBQ; TestPoint_Pad_4.0x4.0mm
TP4: DATA; TestPoint_Pad_4.0x4.0mm
TP5: VCC; TestPoint_Pad_4.0x4.0mm
TP6: GND; TestPoint_Pad_4.0x4.0mm
U1: ATtiny85-20PU; DIP-8_W7.62mm_Socket; Part Microchip ATTINY85-20PU in a TE 1-21992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

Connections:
/DATA: TP4.1, U1.7 (PB2)
/GND: C1.2, TP6.1, U1.4 (GND)
/RST: R1.1, U1.1 (~RESET/PB5)
/SQCK: TP2.1, U1.5 (AREF/PB0)
/SUBQ: TP3.1, U1.6 (PB1)
/VCC: C1.1, R1.2, TP5.1, U1.8 (VCC)
/WFCK: TP1.1, U1.3 (XTAL2/PB4)

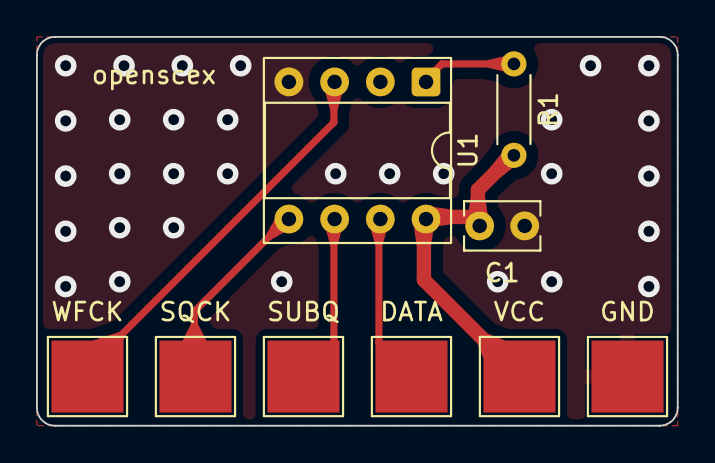
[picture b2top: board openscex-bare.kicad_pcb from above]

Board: 2 copper layers, 35.6 x 21.6 mm, 9 parts (0 on the bottom side), 7 nets.

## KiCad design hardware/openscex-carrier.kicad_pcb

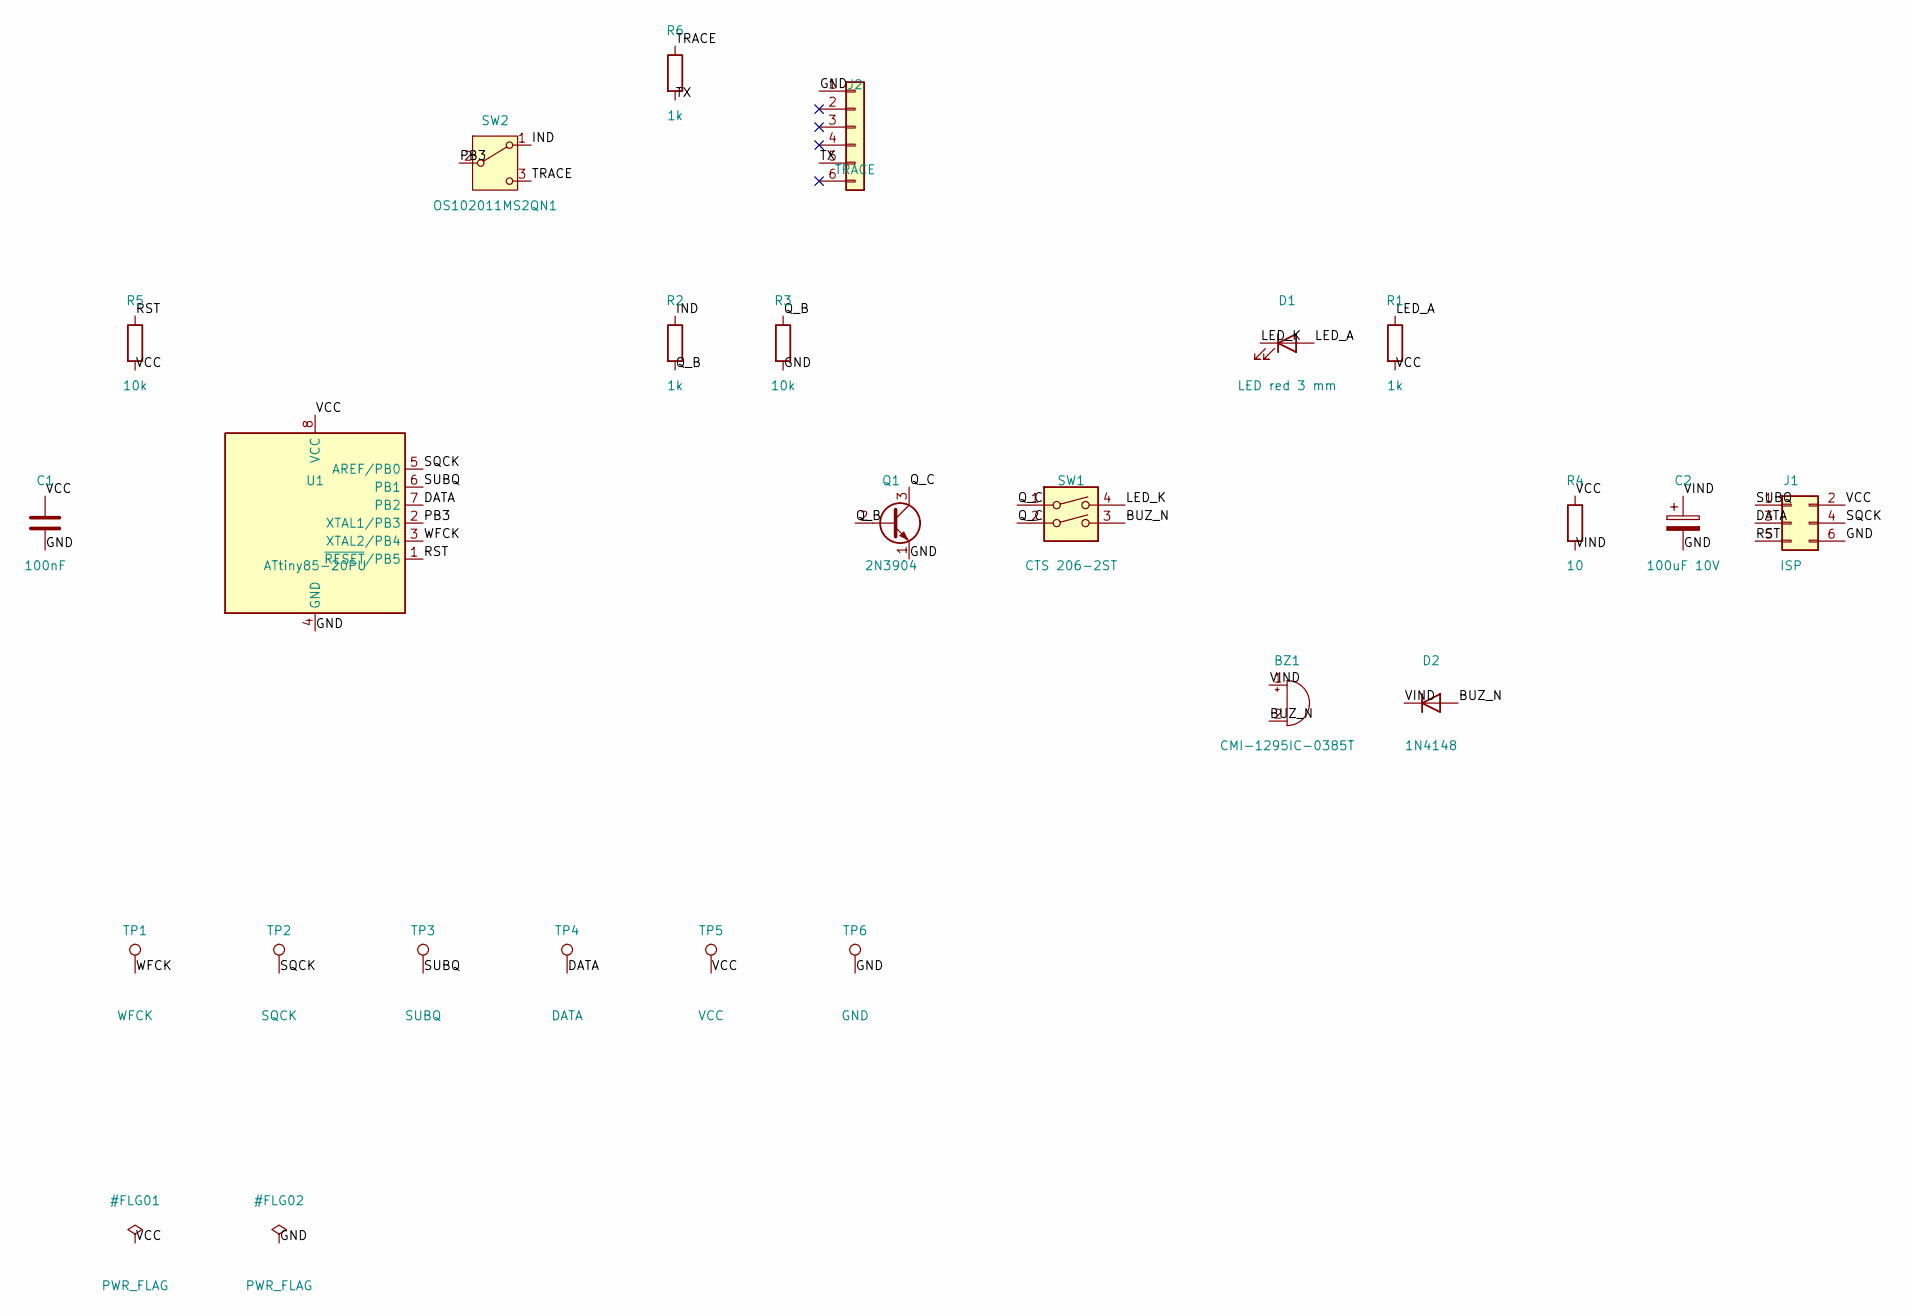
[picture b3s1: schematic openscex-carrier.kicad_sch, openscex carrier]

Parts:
BZ1: CMI-1295IC-0385T; Buzzer_12x9.5RM7.6_CMI-1295IC-0385T; Part Same Sky CMI-1295IC-0385T magnetic buzz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
C1: 100nF; C_Rect_L4.0mm_W2.5mm_P2.50mm; Part KEMET C315C104K5R5TA, 100 nF 50 V X7R, 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
C2: 100uF 10V; CP_Radial_D5.0mm_P2.00mm; Part Panasonic EEU-FC1A101S, 100 uF 10 V, 10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
D1: LED red 3 mm; LED_D3.0mm; Part Kingbright WP710A10ID, 3 mm red LED
D2: 1N4148; D_DO-35_SOD27_P7.62mm_Horizontal; Part onsemi 1N4148TR, DO-35
J1: ISP; IDC-Header_2x03_P2.54mm_Vertical_Wurth_61200621621; Part Wurth 61200621621, 2x3 box header, 2.54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
J2: TRACE; PinHeader_1x06_P2.54mm_Vertical; Part Wurth 61300611121, 1x6 pin header, 2.54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
Q1: 2N3904; TO-92_Inline_Wide; Part onsemi 2N3904RLRAG, TO-92 with bent lea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
R1, R2, R6: 1k; R_Axial_DIN0204_L3.6mm_D1.6mm_P5.08mm_Horizontal; Part Vishay MBA02040C1001FC100, 1 kOhm 1 % 0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
R3, R5: 10k; R_Axial_DIN0204_L3.6mm_D1.6mm_P5.08mm_Horizontal; Part Vishay MBA02040C1002FC100, 10 kOhm 1 % 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
R4: 10; R_Axial_DIN0204_L3.6mm_D1.6mm_P5.08mm_Horizontal; Part Vishay MBA02040C1009FC100, 10 Ohm 1 % 0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
SW1: CTS 206-2ST; SW_DIP_SPSTx02_Slide_9.78x7.26mm_W7.62mm_P2.54mm; Part CTS 206-2ST, 2-position DIP switch
SW2: OS102011MS2QN1; SW_Slide_SPDT_Straight_CK_OS102011MS2Q; Part C&K OS102011MS2QN1, SPDT slide switch, 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
TP1: WFCK; TestPoint_Pad_4.0x4.0mm
TP2: SQCK; TestPoint_Pad_4.0x4.0mm
TP3: SUBQ; TestPoint_Pad_4.0x4.0mm
TP4: DATA; TestPoint_Pad_4.0x4.0mm
TP5: VCC; TestPoint_Pad_4.0x4.0mm
TP6: GND; TestPoint_Pad_4.0x4.0mm
U1: ATtiny85-20PU; DIP-8_W7.62mm_Socket; Part Microchip ATTINY85-20PU in a TE 1-21992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

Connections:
/BUZ_N: BZ1.2 (-), D2.2 (A), SW1.3
/DATA: J1.3, TP4.1, U1.7 (PB2)
/GND: C1.2, C2.2, J1.6, J2.1, Q1.1 (E), R3.2, TP6.1, U1.4 (GND)
/IND: R2.1, SW2.1 (A)
/LED_A: D1.2 (A), R1.1
/LED_K: D1.1 (K), SW1.4
/PB3: SW2.2 (B), U1.2 (XTAL1/PB3)
/Q_B: Q1.2 (B), R2.2, R3.1
/Q_C: Q1.3 (C), SW1.1, SW1.2
/RST: J1.5, R5.1, U1.1 (~RESET/PB5)
/SQCK: J1.4, TP2.1, U1.5 (AREF/PB0)
/SUBQ: J1.1, TP3.1, U1.6 (PB1)
/TRACE: R6.1, SW2.3 (C)
/TX: J2.5, R6.2
/VCC: C1.1, J1.2, R1.2, R4.1, R5.2, TP5.1, U1.8 (VCC)
/VIND: BZ1.1 (+), C2.1, D2.1 (K), R4.2
/WFCK: TP1.1, U1.3 (XTAL2/PB4)

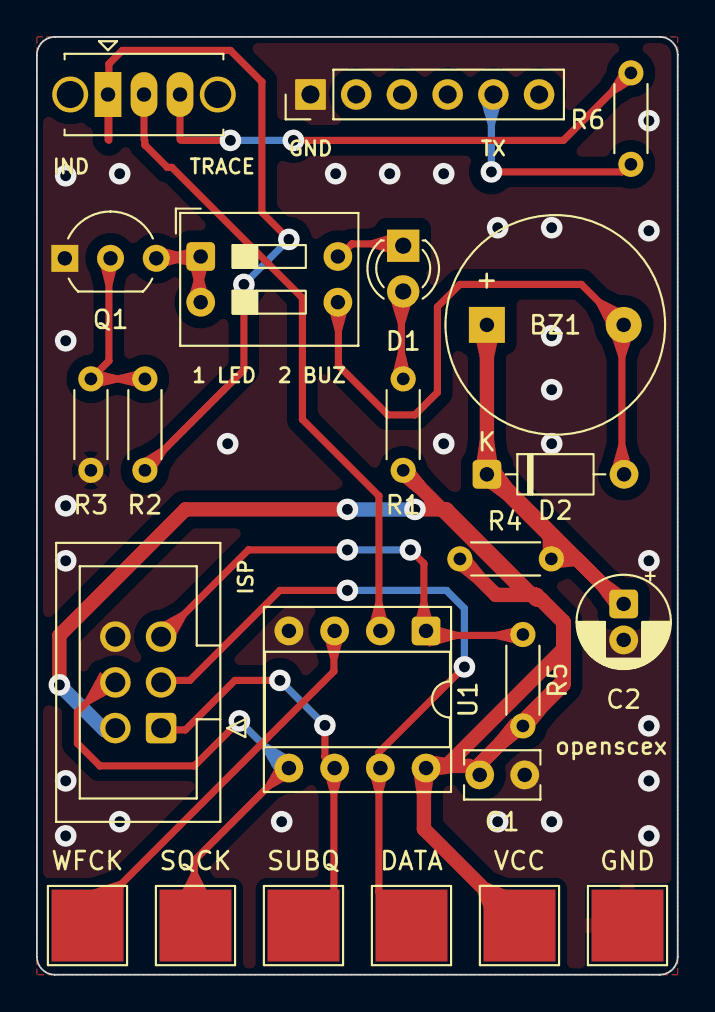
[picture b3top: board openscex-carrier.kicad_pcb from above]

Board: 2 copper layers, 35.6 x 52.1 mm, 23 parts (0 on the bottom side), 17 nets.

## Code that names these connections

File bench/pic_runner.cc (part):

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// Console wires a chip may not use; the timeline drives them for every chip,
// and one this chip lacks is simply not wired. Any other name is an error.
bool is_console_wire(const std::string &name) {
  for (const char *wire : { "sqck", "subq", "wfck", "lid", "reset", "sense" }) {
    if (name == wire) {
      return true;
    }
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int main(int argc, char **argv) {
  if (argc != 9) {
    std::fprintf(stderr,
                 "usage: %s image processor clock_hz timeline trace coverage duration_ns pins\n",
                 argv[0]);
    return 2;
  }
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  // One node and source per input, starting at the console's idle levels: WFCK
  // high, lid closed, reset released, sense high.
  std::map<std::string, Drive *> drives;
  const char *inputs[] = { "sqck", "subq", "wfck", "lid", "reset", "sense" };
  for (const char *name : inputs) {
    auto found = pins.find(name);
    if (found == pins.end() || found->second.pin == 0) {
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        wfck_half_ns = static_cast<unsigned long long>(event.value);
        next_wfck_ns = event.time_ns + wfck_half_ns;
      } else if (event.signal == "wfck") {
        wfck = event.value != 0;
        drive_line("wfck", wfck);
      } else if (event.signal == "power_cycle") {
        // Power-on reset; the calibration word stays in program memory.
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

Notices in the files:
bench/pic_runner.cc:
SPDX-FileCopyrightText: 2026 Gustavo Franco <gufranco@users.noreply.github.com>
SPDX-License-Identifier: MIT
README.md:
License:
[MIT](LICENSE) for the firmware, the documentation and the board designs in [hardware/](hardware).
The footprints in [hardware/openscex.pretty](hardware/openscex.pretty) start from KiCad's library footprints and keep their licence, [CC-BY-SA-4.0](LICENSES/CC-BY-SA-4.0.txt) with the [KiCad libraries exception](LICENSES/KiCad-libraries-exception.txt): a board made with them carries no obligation. Source: [REUSE.toml](REUSE.toml).
